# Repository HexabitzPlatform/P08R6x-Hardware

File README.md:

# P08R6x-Hardware
Hexabitz VL53L8 Time-of-Flight IR Sensor Module Hardware Design

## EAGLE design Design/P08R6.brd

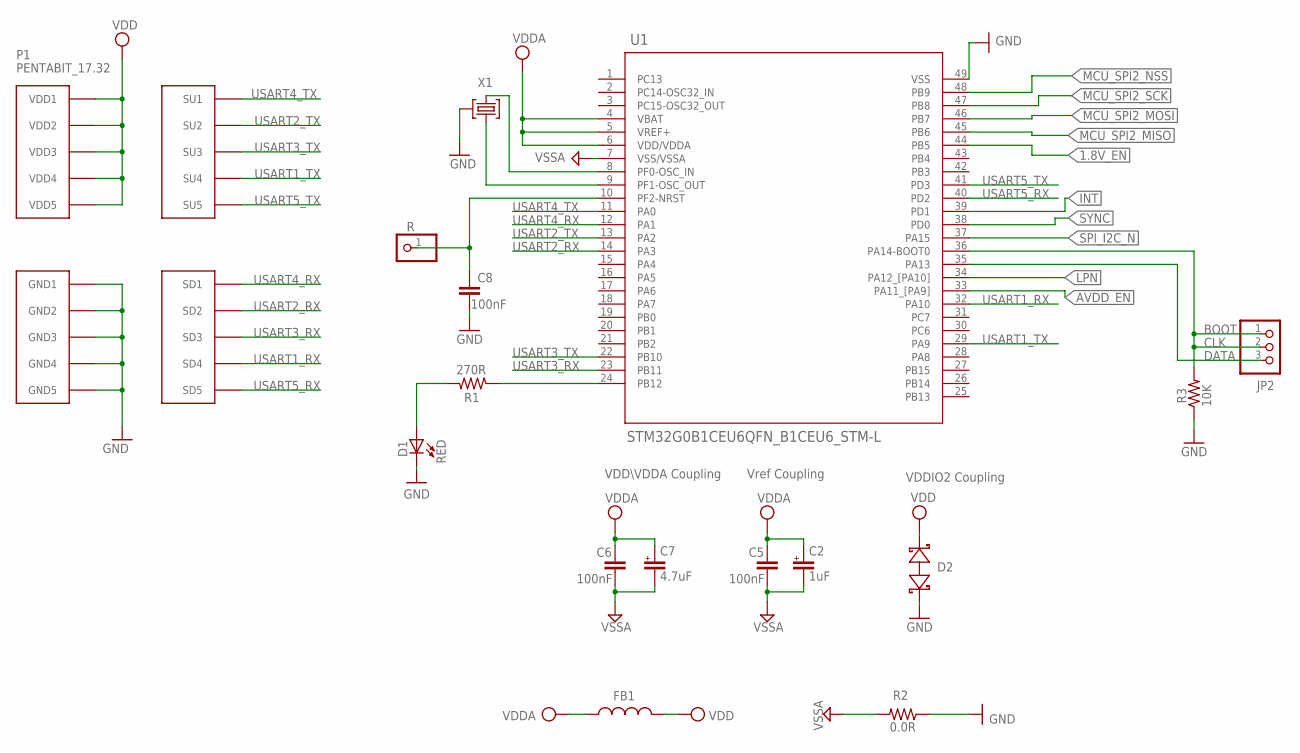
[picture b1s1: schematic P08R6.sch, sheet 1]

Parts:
C2: 1uF; C-0603-POL
C5, C6, C8: 100nF; C-0402
C7: 4.7uF; C-0603-POL
D1: RED; VLMS1300-GS08; MPN VLMS1300-GS08
D2: BOURNS_CDSOD323-T03SCBOURNS_CDSOD323-T03SC_0_0; BOURNS_CDSOD323-T03SC_0
FB1: FB-TDK_MMZ1608Y300B; FB-0603; MPN MMZ1608Y300B
JP2: PINHD-1X3; 1X03
P1: PENTABIT_17.32
R: R; 1X01
R1: 270R; R-0402
R2: 0.0R; R-0402; MPN RC0603JR-070RL
R3: 10K; R-0402
TRIMBLE-LOGO1: HEXA-LOGO
U1: STM32G0B1CEU6QFN_B1CEU6_STM-L; QFN_B1CEU6_STM-L
X1: XTALL_CSTCE8M00G52

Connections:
1.8V_EN: U1.44 (PB5); also elsewhere on the board
AVDD_EN: U1.33 (PA11_[PA9]); also elsewhere on the board
CLK: JP2.1, JP2.2, R3.2, U1.36 (PA14-BOOT0)
DATA: JP2.3, U1.35 (PA13)
GND: C8.2, D1.C, D2.2 (C), P1.PAD_PD6 (GND1), P1.PAD_PD7 (GND2), P1.PAD_PD8 (GND3), P1.PAD_PD9 (GND4), P1.PAD_PD10 (GND5), R2.1, R3.1, U1.49 (VSS), X1.P$2 (2); also elsewhere on the board
INT: U1.39 (PD1); also elsewhere on the board
LPN: U1.34 (PA12_[PA10]); also elsewhere on the board
MCU_SPI2_MISO: U1.45 (PB6); also elsewhere on the board
MCU_SPI2_MOSI: U1.46 (PB7); also elsewhere on the board
MCU_SPI2_NSS: U1.48 (PB9); also elsewhere on the board
MCU_SPI2_SCK: U1.47 (PB8); also elsewhere on the board
unnamed: D1.A, R1.2
unnamed: C8.1, R.1, U1.10 (PF2-NRST)
unnamed: U1.9 (PF1-OSC_OUT), X1.P$1 (1)
unnamed: U1.8 (PF0-OSC_IN), X1.P$3 (3)
unnamed: R1.1, U1.24 (PB12)
SPI_I2C_N: U1.37 (PA15); also elsewhere on the board
SYNC: U1.38 (PD0); also elsewhere on the board
USART1_RX: P1.PAD_PD4 (SD4), U1.32 (PA10)
USART1_TX: P1.PAD_PU4 (SU4), U1.29 (PA9)
USART2_RX: P1.PAD_PD2 (SD2), U1.14 (PA3)
USART2_TX: P1.PAD_PU2 (SU2), U1.13 (PA2)
USART3_RX: P1.PAD_PD3 (SD3), U1.23 (PB11)
USART3_TX: P1.PAD_PU3 (SU3), U1.22 (PB10)
USART4_RX: P1.PAD_PD1 (SD1), U1.12 (PA1)
USART4_TX: P1.PAD_PU1 (SU1), U1.11 (PA0)
USART5_RX: P1.PAD_PD5 (SD5), U1.40 (PD2)
USART5_TX: P1.PAD_PU5 (SU5), U1.41 (PD3)
VDD: D2.1 (A), FB1.2, P1.PAD_PU6 (VDD1), P1.PAD_PU7 (VDD2), P1.PAD_PU8 (VDD3), P1.PAD_PU9 (VDD4), P1.PAD_PU10 (VDD5); also elsewhere on the board
VDDA: C2.1, C5.1, C6.1, C7.1, FB1.1, U1.4 (VBAT), U1.5 (VREF+), U1.6 (VDD/VDDA)
VSSA: C2.2, C5.2, C6.2, C7.2, R2.2, U1.7 (VSS/VSSA)

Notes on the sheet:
Vref Coupling
VDDIO2 Coupling
VDD\VDDA Coupling
BOOT

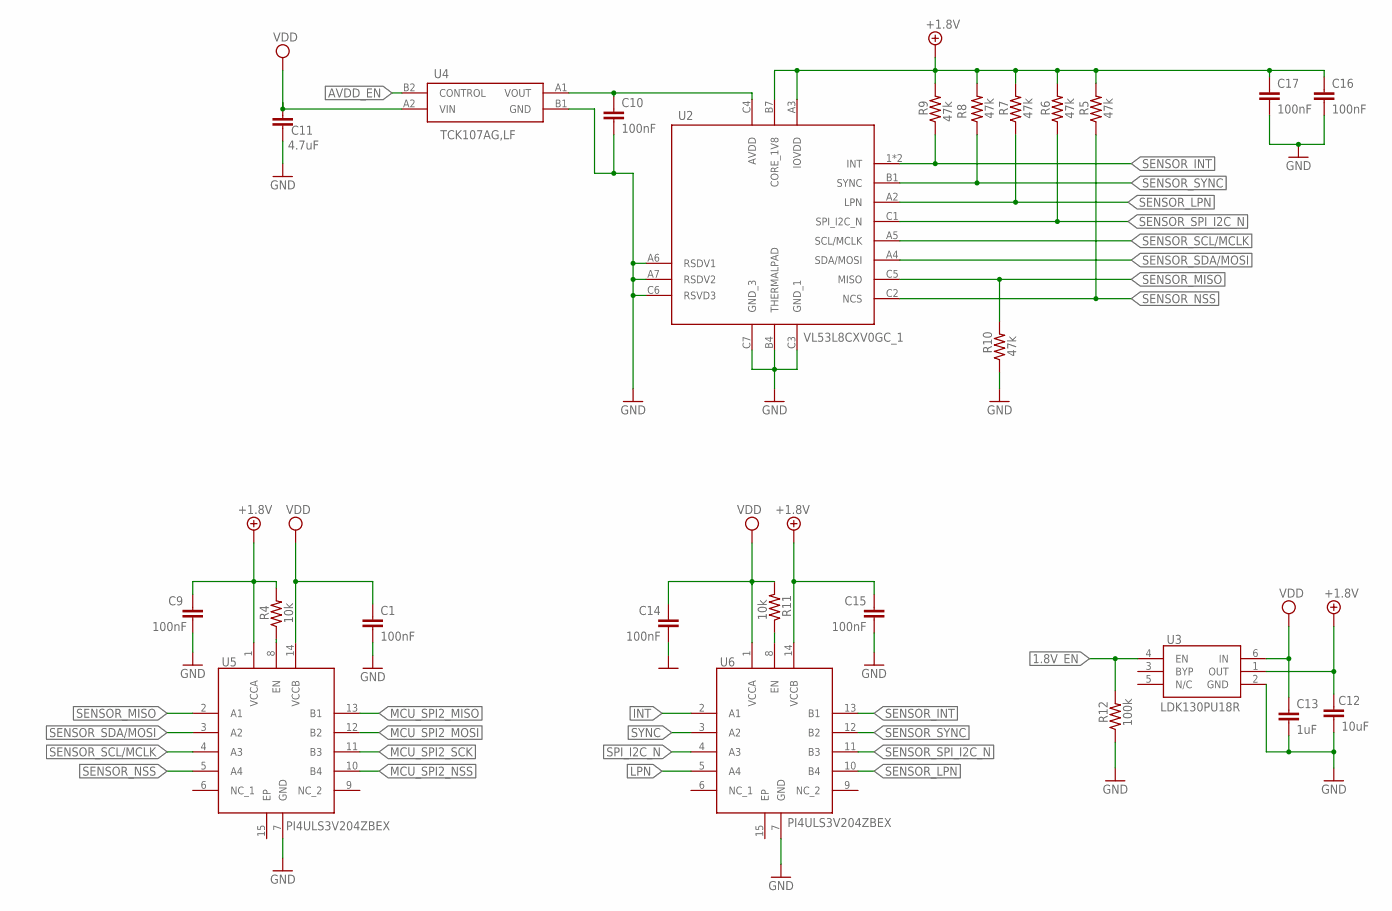
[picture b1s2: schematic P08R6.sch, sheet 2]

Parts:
C1, C9, C10, C14, C15, C16, C17: 100nF; C-0402
C11: 4.7uF; C-0603
C12: 10uF; C-0402
C13: 1uF; C-0402
R4, R11: 10k; R-0402
R5, R6, R7, R8, R9, R10: 47k; R-0402
R12: 100k; R-0402
U2: VL53L8CXV0GC_1; VL53L8CXV0GC1
U3: LDK130PU18R
U4: TCK107AG,LF; BGA4C40P2X2_79X79X59
U5, U6: PI4ULS3V204ZBEX

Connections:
1.8V_EN: R12.2, U3.4 (EN); also elsewhere on the board
+1.8V: C9.1, C12.1, C15.1, C16.1, C17.1, R4.2, R5.2, R6.2, R7.2, R8.2, R9.2, U2.A3 (IOVDD), U2.B7 (CORE_1V8), U3.1 (OUT), U5.1 (VCCA), U6.14 (VCCB)
AVDD_EN: U4.B2 (CONTROL); also elsewhere on the board
CONTROLLED_AVDD: C10.1, U2.C4 (AVDD), U4.A1 (VOUT)
GND: C1.2, C9.2, C10.2, C11.2, C12.2, C13.2, C14.2, C15.2, C16.2, C17.2, R10.1, R12.1, U2.A6 (RSDV1), U2.A7 (RSDV2), U2.B4 (THERMALPAD), U2.C3 (GND_1), U2.C6 (RSVD3), U2.C7 (GND_3), U3.2 (GND), U4.B1 (GND), U5.7 (GND), U6.7 (GND); also elsewhere on the board
INT: U6.2 (A1); also elsewhere on the board
LPN: U6.5 (A4); also elsewhere on the board
MCU_SPI2_MISO: U5.13 (B1); also elsewhere on the board
MCU_SPI2_MOSI: U5.12 (B2); also elsewhere on the board
MCU_SPI2_NSS: U5.10 (B4); also elsewhere on the board
MCU_SPI2_SCK: U5.11 (B3); also elsewhere on the board
unnamed: R4.1, U5.8 (EN)
unnamed: R11.1, U6.8 (EN)
SENSOR_INT: R9.1, U2.1 (INT), U2.A1 (INT), U6.13 (B1)
SENSOR_LPN: R7.1, U2.A2 (LPN), U6.10 (B4)
SENSOR_MISO: R10.2, U2.C5 (MISO), U5.2 (A1)
SENSOR_NSS: R5.1, U2.C2 (NCS), U5.5 (A4)
SENSOR_SCL/MCLK: U2.A5 (SCL/MCLK), U5.4 (A3)
SENSOR_SDA/MOSI: U2.A4 (SDA/MOSI), U5.3 (A2)
SENSOR_SPI_I2C_N: R6.1, U2.C1 (SPI_I2C_N), U6.11 (B3)
SENSOR_SYNC: R8.1, U2.B1 (SYNC), U6.12 (B2)
SPI_I2C_N: U6.4 (A3); also elsewhere on the board
SYNC: U6.3 (A2); also elsewhere on the board
VDD: C1.1, C11.1, C13.1, C14.1, R11.2, U3.6 (IN), U4.A2 (VIN), U5.14 (VCCB), U6.1 (VCCA); also elsewhere on the board

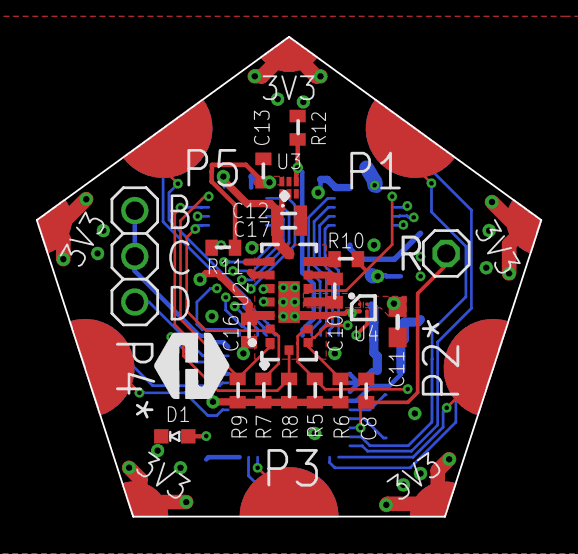
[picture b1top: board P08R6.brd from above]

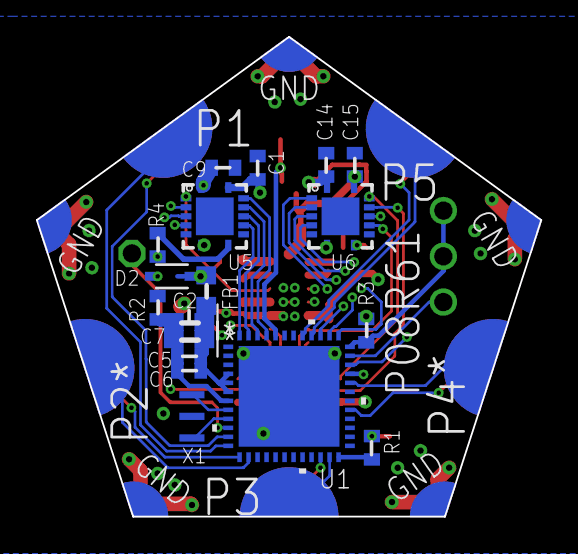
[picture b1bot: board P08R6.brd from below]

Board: 4 copper layers, 28.0 x 26.6 mm, 41 parts (18 on the bottom side), 43 nets.

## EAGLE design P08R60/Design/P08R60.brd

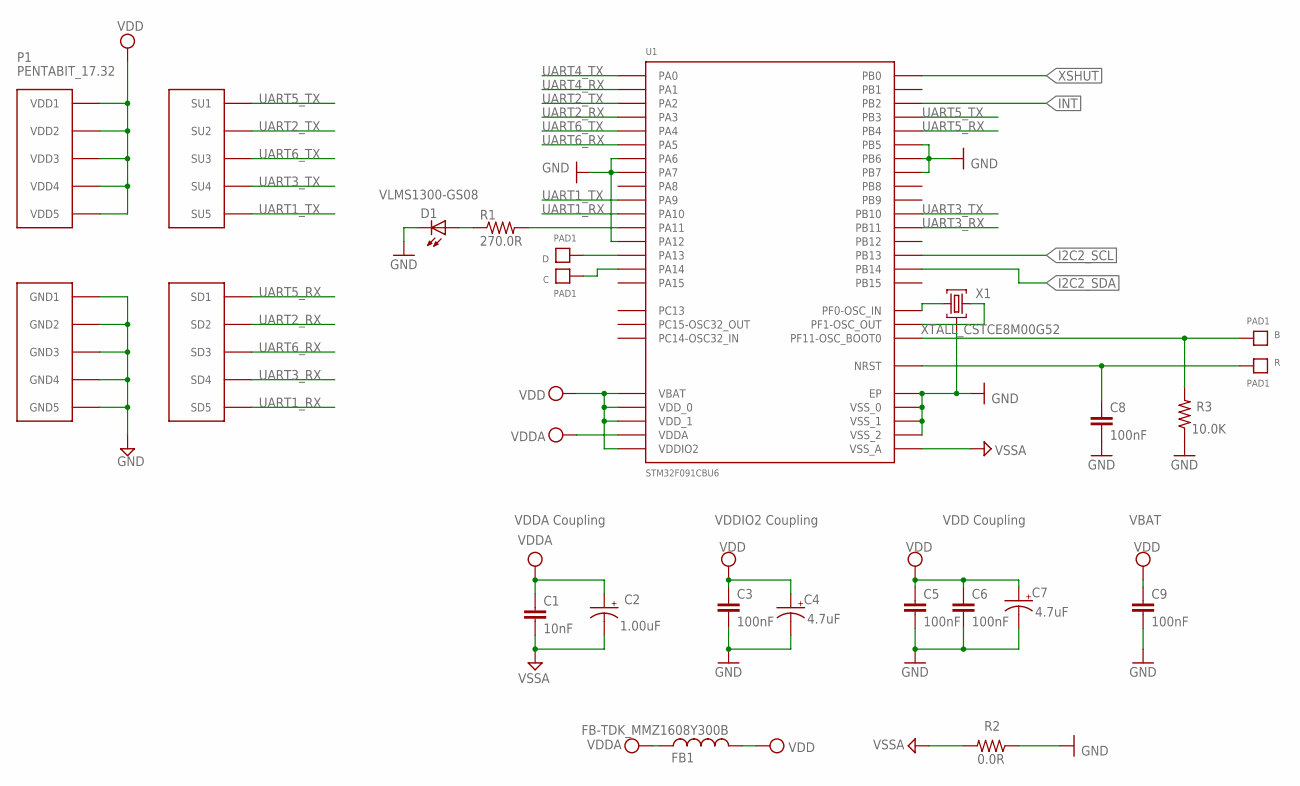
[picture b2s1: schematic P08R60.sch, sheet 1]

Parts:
B: PAD1
C: PAD1
C1: 10nF; C-0603; TOLERANCE 10%; VOLTAGE_RATING 50V; MPN C0603C103K5RACTU
C2: 1.00uF; C-0805-POL; TOLERANCE 10%; VOLTAGE_RATING 16V; MPN CC0805KKX7R7BB105
C3, C6, C8: 100nF; C-0603; TOLERANCE 10%; VOLTAGE_RATING 10V; MPN C0603C104K8RACTU
C4, C7: 4.7uF; C-0805-POL; TOLERANCE 10%; VOLTAGE_RATING 25V; MPN GRM21BC81E475KA12L
C5: 100nF; C-0603; TOLERANCE 10%; VOLTAGE_RATING 10; MPN C0603C104K8RACTU
C9: 100nF; C-0603; TOLERANCE 10V; VOLTAGE_RATING 10%; MPN C0603C104K8RACTU
D: PAD1
D1: VLMS1300-GS08; MPN VLMS1300-GS08
FB1: FB-TDK_MMZ1608Y300B; MPN MMZ1608Y300B
P1: PENTABIT_17.32
R: PAD1
R1: 270.0R; R-0603; TOLERANCE 1%; MPN RC0603FR-07270RL
R2: 0.0R; R-0603; MPN RC0603JR-070RL
R3: 10.0K; R-0603; TOLERANCE 5%; MPN RC0603JR-0710KL
U1: STM32F091CBU6
X1: XTALL_CSTCE8M00G52

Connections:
B1: B.P$1, B.P$2, R3.2, U1.P$44 (PF11-OSC_BOOT0)
GND: C3.2, C4.2 (-), C5.2, C6.2, C7.2 (-), C8.2, C9.2, D1.C, P1.PAD_PD6 (GND1), P1.PAD_PD7 (GND2), P1.PAD_PD8 (GND3), P1.PAD_PD9 (GND4), P1.PAD_PD10 (GND5), R2.1, R3.1, U1.EP, U1.P$16 (PA6), U1.P$17 (PA7), U1.P$23 (VSS_0), U1.P$33 (PA12), U1.P$35 (VSS_1), U1.P$41 (PB5), U1.P$42 (PB6), U1.P$43 (PB7), U1.P$47 (VSS_2), X1.P$2 (2); also elsewhere on the board
I2C2_SCL: U1.P$26 (PB13); also elsewhere on the board
I2C2_SDA: U1.P$27 (PB14); also elsewhere on the board
INT: U1.P$20 (PB2); also elsewhere on the board
unnamed: R1.2, U1.P$32 (PA11)
unnamed: D1.A, R1.1
unnamed: U1.P$5 (PF0-OSC_IN), X1.P$1 (1)
unnamed: U1.P$6 (PF1-OSC_OUT), X1.P$3 (3)
unnamed: D.P$1, D.P$2, U1.P$34 (PA13)
unnamed: C.P$1, C.P$2, U1.P$37 (PA14)
R1: C8.1, R.P$1, R.P$2, U1.P$7 (NRST)
UART1_RX: P1.PAD_PD5 (SD5), U1.P$31 (PA10)
UART1_TX: P1.PAD_PU5 (SU5), U1.P$30 (PA9)
UART2_RX: P1.PAD_PD2 (SD2), U1.P$13 (PA3)
UART2_TX: P1.PAD_PU2 (SU2), U1.P$12 (PA2)
UART3_RX: P1.PAD_PD4 (SD4), U1.P$22 (PB11)
UART3_TX: P1.PAD_PU4 (SU4), U1.P$21 (PB10)
UART4_RX: U1.P$11 (PA1)
UART4_TX: U1.P$10 (PA0)
UART5_RX: P1.PAD_PD1 (SD1), U1.P$40 (PB4)
UART5_TX: P1.PAD_PU1 (SU1), U1.P$39 (PB3)
UART6_RX: P1.PAD_PD3 (SD3), U1.P$15 (PA5)
UART6_TX: P1.PAD_PU3 (SU3), U1.P$14 (PA4)
VDD: C3.1, C4.1 (+), C5.1, C6.1, C7.1 (+), C9.1, FB1.2, P1.PAD_PU6 (VDD1), P1.PAD_PU7 (VDD2), P1.PAD_PU8 (VDD3), P1.PAD_PU9 (VDD4), P1.PAD_PU10 (VDD5), U1.P$1 (VBAT), U1.P$24 (VDD_0), U1.P$36 (VDDIO2), U1.P$48 (VDD_1); also elsewhere on the board
VDDA: C1.1, C2.1 (+), FB1.1, U1.P$9 (VDDA)
VSSA: C1.2, C2.2 (-), R2.2, U1.P$8 (VSS_A)
XSHUT: U1.P$18 (PB0); also elsewhere on the board

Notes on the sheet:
VDDA Coupling
VDDIO2 Coupling
VDD Coupling
VBAT

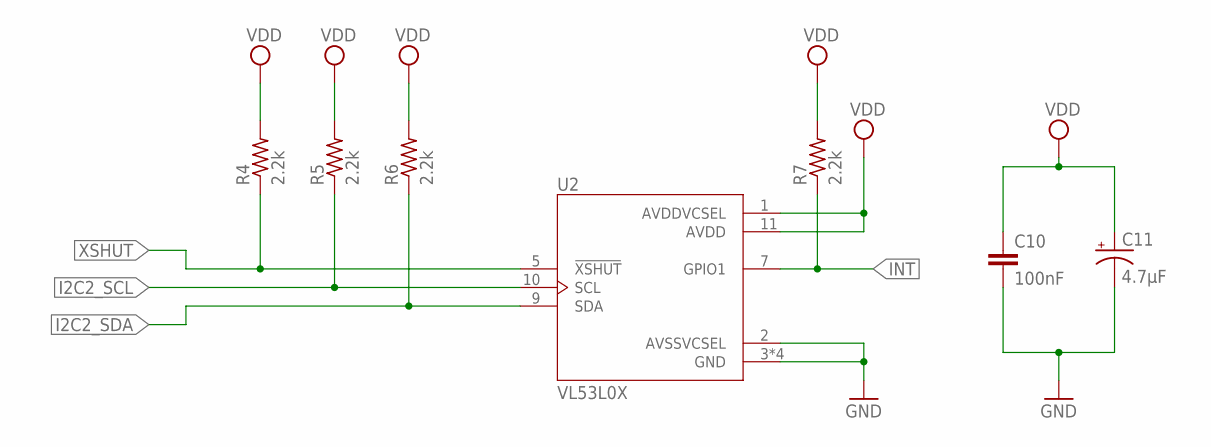
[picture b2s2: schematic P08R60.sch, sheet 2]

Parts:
C10: 100nF; C-0603; TOLERANCE ±10%; VOLTAGE_RATING 16.0 V; MPN C0603C104K8RACTU
C11: 4.7uF; C-0805; TOLERANCE 10%; VOLTAGE_RATING 25V; MPN GRM21BC81E475KA12L
R4, R5, R6, R7: 2.2k; R-0603; TOLERANCE ±1%; MPN CRCW06032K20FKEA
U2: VL53L0X; SENSOR_VL53L0X

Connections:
GND: C10.2, C11.2 (-), U2.2 (AVSSVCSEL), U2.3 (GND), U2.4 (GND), U2.6 (GND), U2.12 (GND); also elsewhere on the board
I2C2_SCL: R5.1, U2.10 (SCL); also elsewhere on the board
I2C2_SDA: R6.1, U2.9 (SDA); also elsewhere on the board
INT: R7.1, U2.7 (GPIO1); also elsewhere on the board
VDD: C10.1, C11.1 (+), R4.2, R5.2, R6.2, R7.2, U2.1 (AVDDVCSEL), U2.11 (AVDD); also elsewhere on the board
XSHUT: R4.1, U2.5 (!XSHUT); also elsewhere on the board

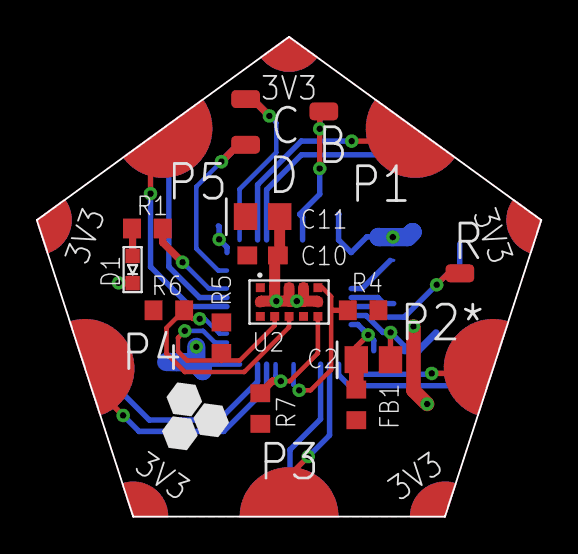
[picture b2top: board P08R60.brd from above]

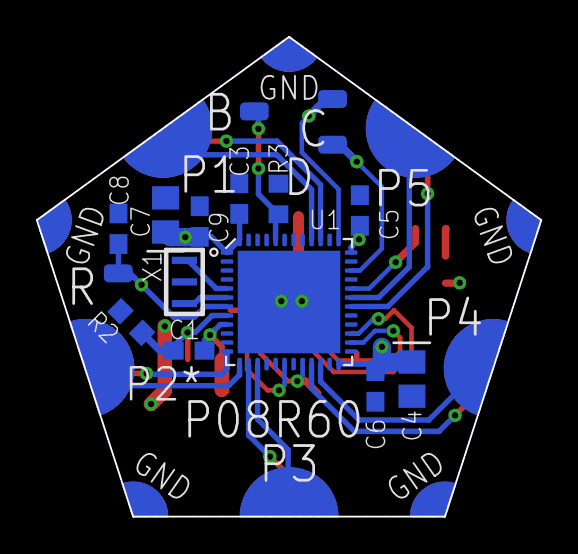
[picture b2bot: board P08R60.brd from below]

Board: 2 copper layers, 28.0 x 26.7 mm, 28 parts (12 on the bottom side), 26 nets.

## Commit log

2019-06-03 Port Schematics from H08 and route some signals
2019-06-05 Module ready for Rev 0 release
    Finish routing the module
    Generate output files
2019-06-05 Adding git ignore
    Copying files into folder
2019-07-01 Fix R4 to R7 PN
2019-08-09 Regenerate Schematics PDF file
2024-12-11 no message
2024-12-11 -The final design, all done. -Upgrade the IR sensor and use VL53L8 - Changing the MCU to STM32G0.
2024-12-26 Add the TVS to the bom

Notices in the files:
parts and their libraries:
COPYRIGHT: Copyright (C) 2021 Ultra Librarian. All rights reserved.
